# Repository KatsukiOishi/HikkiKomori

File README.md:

# 2022-KawasakiRobot
2022年かわさきロボット

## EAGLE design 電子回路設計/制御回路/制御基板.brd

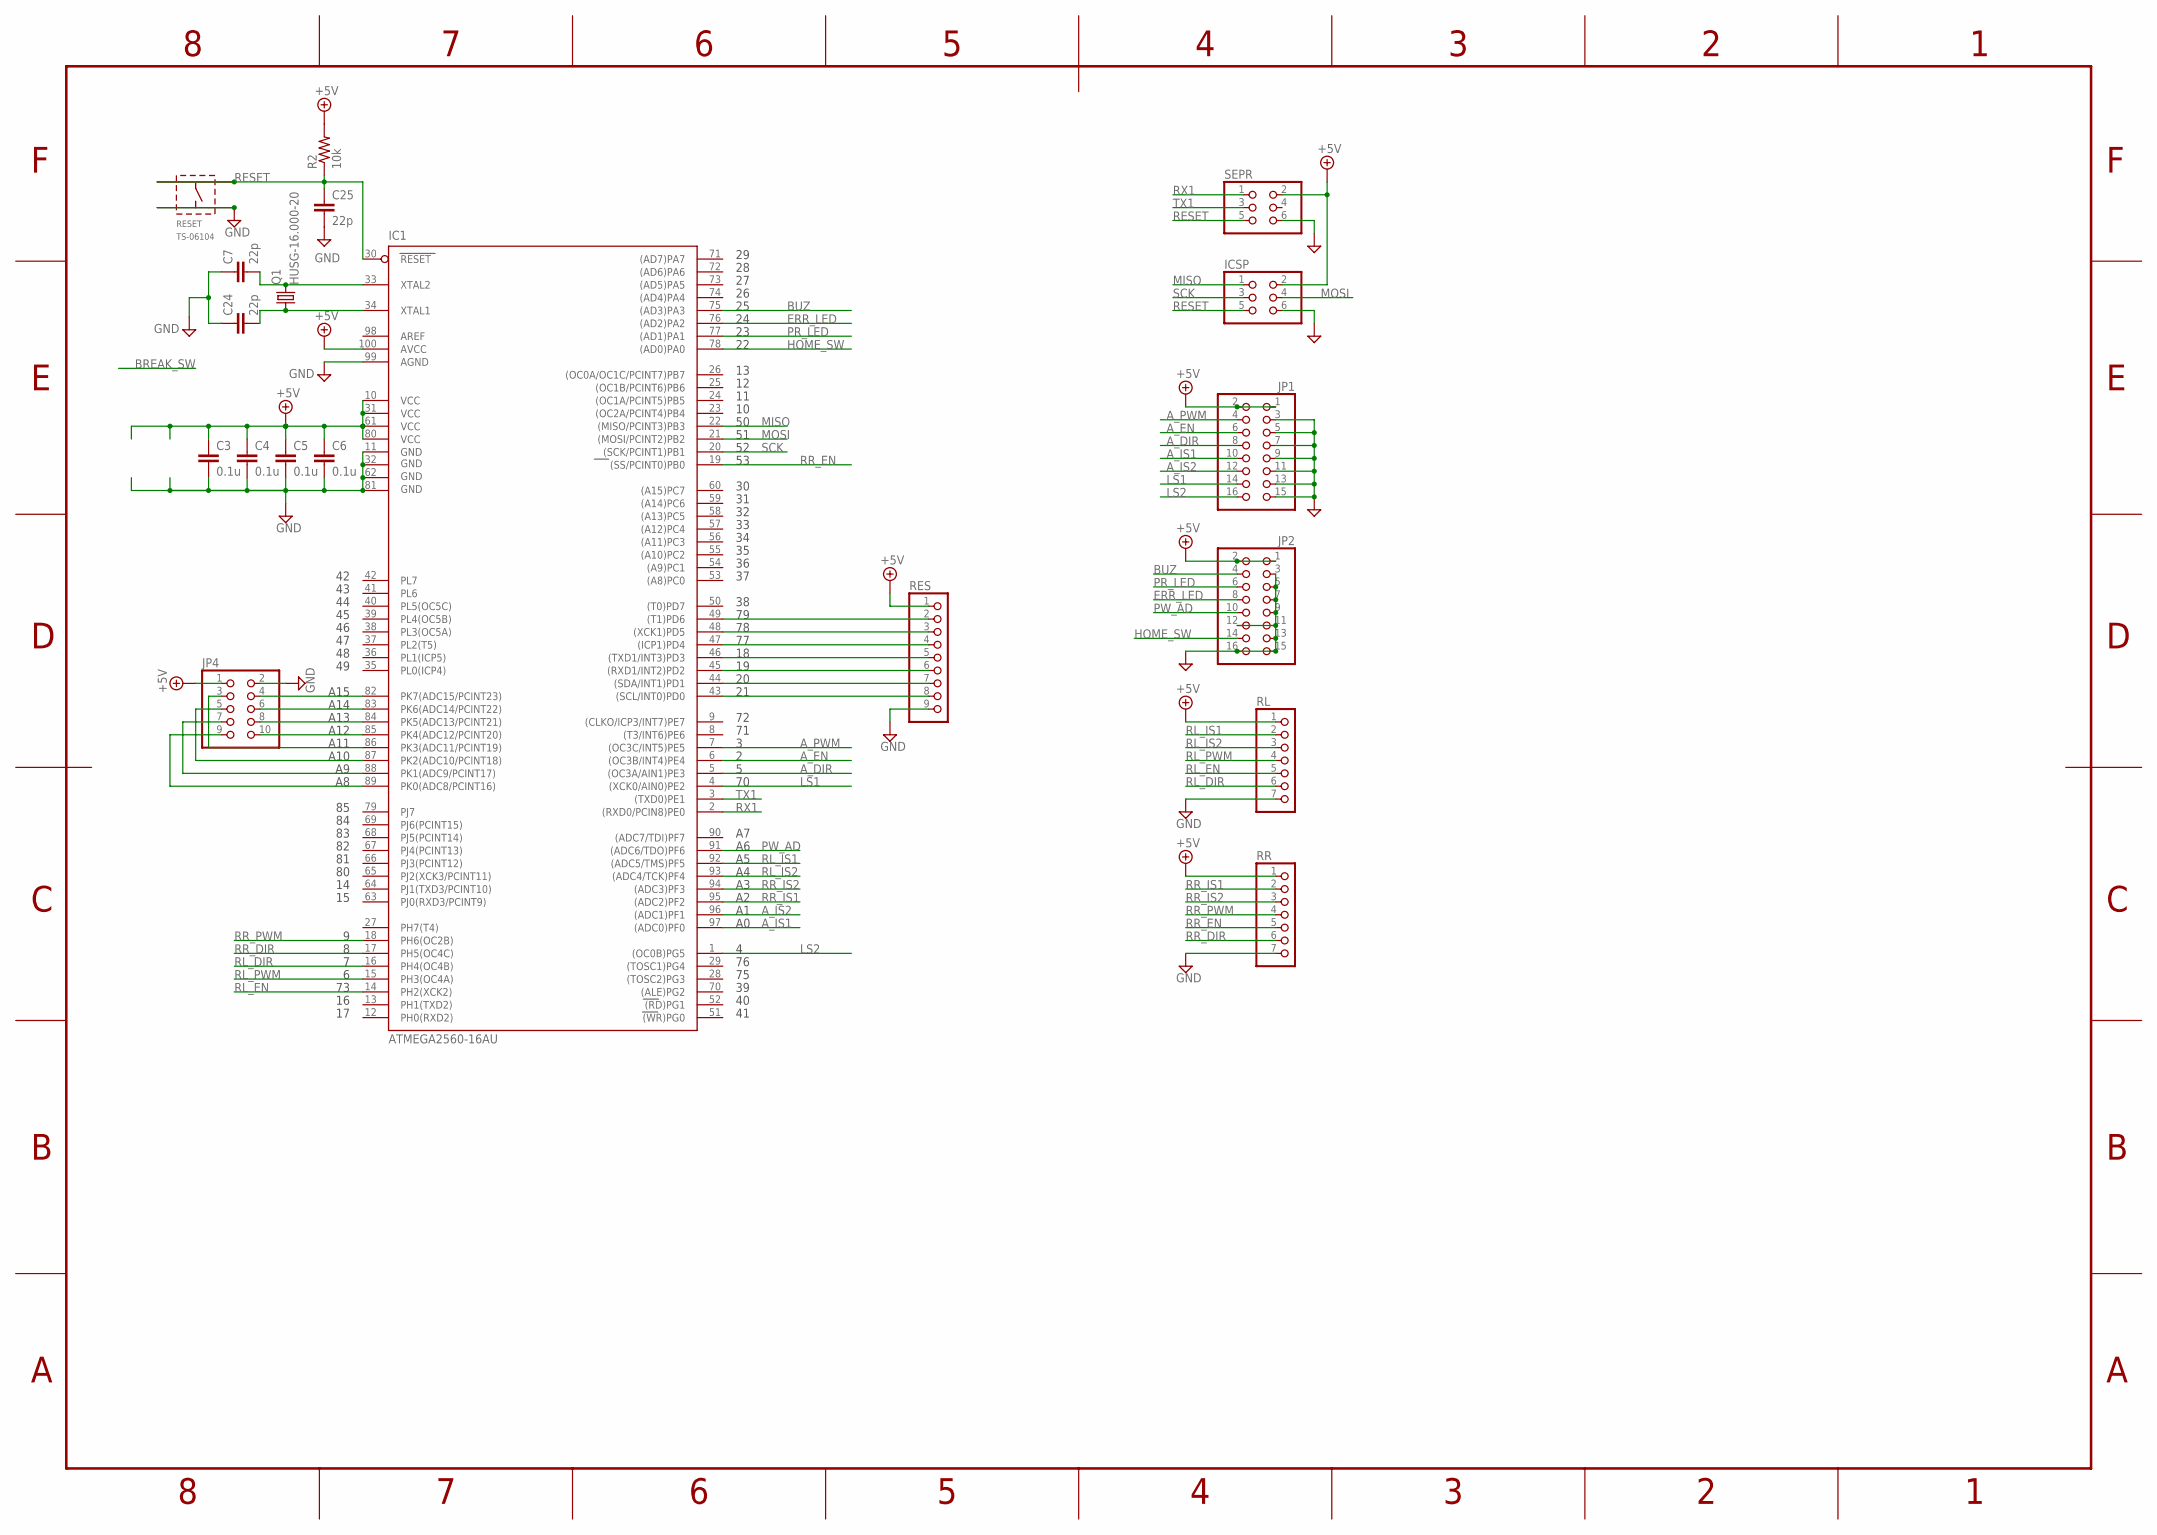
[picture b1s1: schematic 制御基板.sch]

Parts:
C3, C4, C5, C6: 0.1u; C0603
C7, C24, C25: 22p; C0603
IC1: ATMEGA2560-16AU; QFP100
ICSP: PINHD-2X3; 2X03
JP1, JP2: PINHD-2X8; 2X08
JP4: PINHD-2X5; 2X05
Q1: HUSG-16.000-20; XTALRR480W50L990T368H350B
R2: 10k; R0603
RES: PINHD-1X9; 1X09
RESET: TS-06104
RL: PINHD-1X7; 1X07
RR: PINHD-1X7; 1X07
SEPR: PINHD-2X3; 2X03

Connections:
+5V: C3.1, C4.1, C5.1, C6.1, IC1.10 (VCC), IC1.31 (VCC1), IC1.61 (VCC2), IC1.80 (VCC3), IC1.100 (AVCC), ICSP.2, JP1.1, JP1.2, JP2.1, JP2.2, JP4.1, R2.2, RES.1, RL.1, RR.1, SEPR.2
A_DIR: IC1.5 ((OC3A/AIN1)PE3), JP1.8
A_EN: IC1.6 ((OC3B/INT4)PE4), JP1.6
A_IS1: IC1.97 ((ADC0)PF0), JP1.10
A_IS2: IC1.96 ((ADC1)PF1), JP1.12
A_PWM: IC1.7 ((OC3C/INT5)PE5), JP1.4
BUZ: IC1.75 ((AD3)PA3), JP2.4
ERR_LED: IC1.76 ((AD2)PA2), JP2.6
GND: C3.2, C4.2, C5.2, C6.2, C7.1, C24.1, C25.2, IC1.11 (GND), IC1.32 (GND1), IC1.62 (GND2), IC1.81 (GND3), IC1.99 (AGND), ICSP.6, JP1.3, JP1.5, JP1.7, JP1.9, JP1.11, JP1.13, JP1.15, JP2.3, JP2.5, JP2.7, JP2.9, JP2.11, JP2.12, JP2.13, JP2.15, JP2.16, JP4.2, RES.9, RESET.B1 (T3), RESET.B2 (T4), RL.7, RR.7, SEPR.6
HOME_SW: IC1.78 ((AD0)PA0), JP2.14
LS1: IC1.4 ((XCK0/AIN0)PE2), JP1.14
LS2: IC1.1 ((OC0B)PG5), JP1.16
MISO: IC1.22 ((MISO/PCINT3)PB3), ICSP.1
MOSI: IC1.21 ((MOSI/PCINT2)PB2), ICSP.4
unnamed: IC1.43 ((SCL/INT0)PD0), RES.8
unnamed: C24.2, IC1.34 (XTAL1), Q1.1
unnamed: C7.2, IC1.33 (XTAL2), Q1.2
unnamed: IC1.44 ((SDA/INT1)PD1), RES.7
unnamed: IC1.45 ((RXD1/INT2)PD2), RES.6
unnamed: IC1.46 ((TXD1/INT3)PD3), RES.5
unnamed: IC1.47 ((ICP1)PD4), RES.4
unnamed: IC1.48 ((XCK1)PD5), RES.3
unnamed: IC1.49 ((T1)PD6), RES.2
unnamed: IC1.89 (PK0(ADC8/PCINT16)), JP4.9
unnamed: IC1.88 (PK1(ADC9/PCINT17)), JP4.7
unnamed: IC1.87 (PK2(ADC10/PCINT18)), JP4.5
unnamed: IC1.86 (PK3(ADC11/PCINT19)), JP4.3
unnamed: IC1.85 (PK4(ADC12/PCINT20)), JP4.10
unnamed: IC1.84 (PK5(ADC13/PCINT21)), JP4.8
unnamed: IC1.83 (PK6(ADC14/PCINT22)), JP4.6
unnamed: IC1.82 (PK7(ADC15/PCINT23)), JP4.4
PR_LED: IC1.77 ((AD1)PA1), JP2.8
PW_AD: IC1.91 ((ADC6/TDO)PF6), JP2.10
RESET: C25.1, IC1.30 (RESET), ICSP.5, R2.1, RESET.A1 (T1), RESET.A2 (T2), SEPR.5
RL_DIR: IC1.16 (PH4(OC4B)), RL.6
RL_EN: IC1.14 (PH2(XCK2)), RL.5
RL_IS1: IC1.92 ((ADC5/TMS)PF5), RL.2
RL_IS2: IC1.93 ((ADC4/TCK)PF4), RL.3
RL_PWM: IC1.15 (PH3(OC4A)), RL.4
RR_DIR: IC1.17 (PH5(OC4C)), RR.6
RR_EN: IC1.19 ((SS/PCINT0)PB0), RR.5
RR_IS1: IC1.95 ((ADC2)PF2), RR.2
RR_IS2: IC1.94 ((ADC3)PF3), RR.3
RR_PWM: IC1.18 (PH6(OC2B)), RR.4
RX1: IC1.2 ((RXD0/PCIN8)PE0), SEPR.1
SCK: IC1.20 ((SCK/PCINT1)PB1), ICSP.3
TX1: IC1.3 ((TXD0)PE1), SEPR.3

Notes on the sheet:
A10
A11
A12
A15
A14
A13

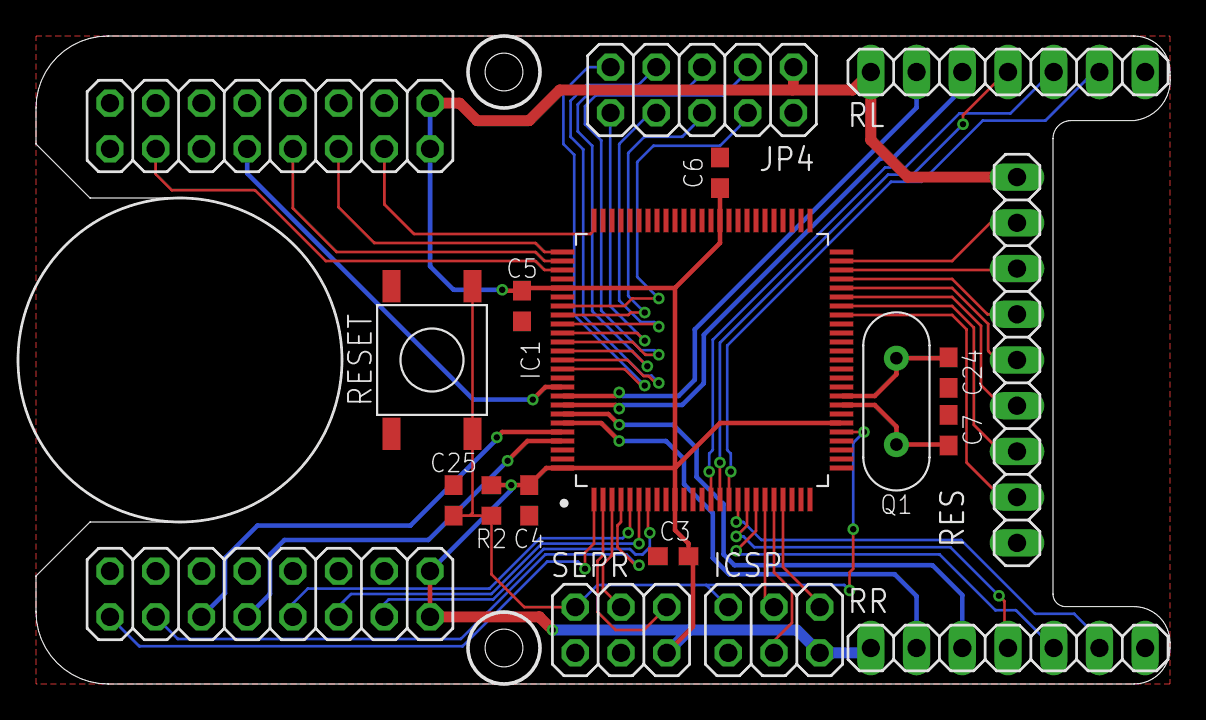
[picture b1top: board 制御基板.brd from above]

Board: 2 copper layers, 63.0 x 36.0 mm, 19 parts (0 on the bottom side), 47 nets.

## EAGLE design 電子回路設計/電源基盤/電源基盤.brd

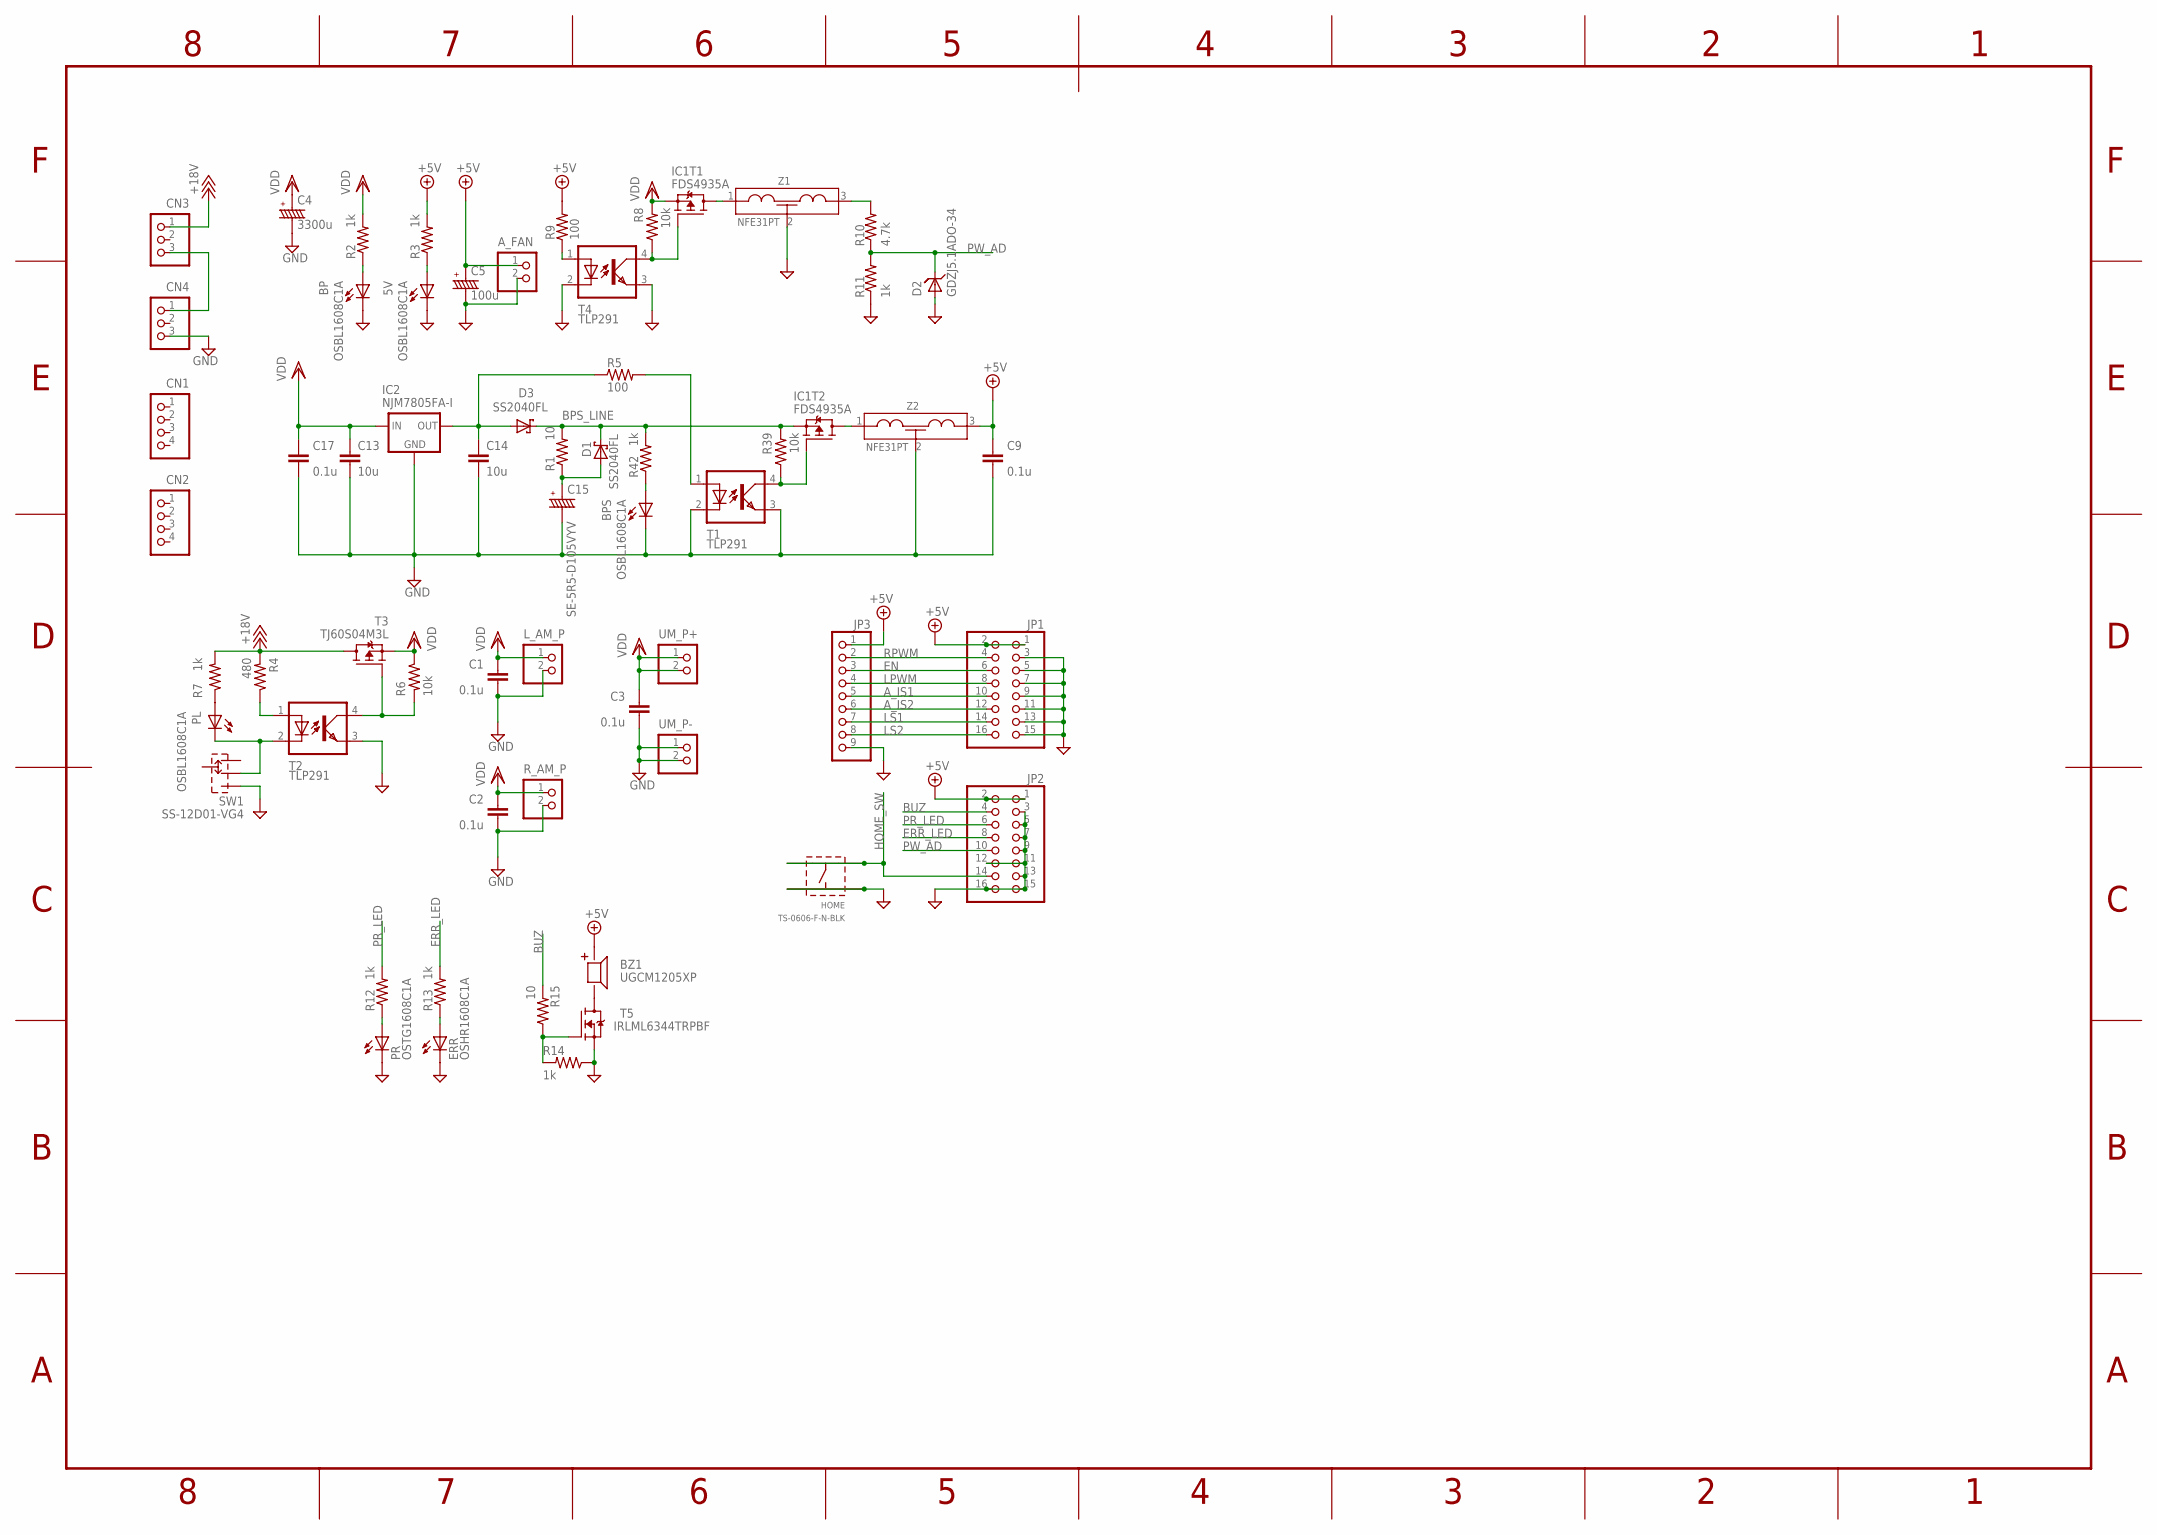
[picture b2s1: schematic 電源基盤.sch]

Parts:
5V: OSBL1608C1A; LEDC1608X39N_B
A_FAN: B2B-XH-A
BP: OSBL1608C1A; LEDC1608X39N_B
BPS: OSBL1608C1A; LEDC1608X39N_B
BZ1: UGCM1205XP
C1, C2, C3, C9, C17: 0.1u; C0603
C4: 3300u; D18_L25_P7.5_D1
C5: 100u; CPOL6.3-7_2.5
C13, C14: 10u; C0805
C15: SE-5R5-D105VYV
CN1, CN2: B4B-XH-A
CN3, CN4: B3P-VH
D1, D3: SS2040FL; SOD-123
D2: GDZJ5.1ADO-34; DIOAD590W50L290D210B
ERR: OSHR1608C1A; LEDC1608X39N_R
HOME: TS-0606-F-N-BLK; TS-0606-F-N
IC1: FDS4935A; SOIC127P600X250-8N
IC2: NJM7805FA-I; TO220
JP1, JP2: PINHD-2X8; 2X08
JP3: PINHD-1X9; 1X09
L_AM_P: B2P-VH
PL: OSBL1608C1A; LEDC1608X39N_B
PR: OSTG1608C1A; LEDC1608X39N_G
R1, R15: 10; R0603
R2, R3, R7, R11, R12, R13, R14, R42: 1k; R0603
R4: 480; R0603
R5, R9: 100; R0603
R6, R8, R39: 10k; R0603
R10: 4.7k; R0603
R_AM_P: B2P-VH
SW1: SS-12D01-VG4
T1, T2, T4: TLP291; SOIC127P700X210-4N
T3: TJ60S04M3L; DPACK
T5: IRLML6344TRPBF; SOT95P240X110-3N
UM_P+: B2P-VH
UM_P-: B2P-VH
Z1, Z2: NFE31PT; NFE31

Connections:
5V1: IC1.7 (D), IC1.8 (D), Z2.1
+5V: A_FAN.1, BZ1.+, C5.+, C9.1, JP1.1, JP1.2, JP2.1, JP2.2, JP3.1, R3.2, R9.2, Z2.3
+18V: CN3.1, R4.2, R7.2, T3.2 (D)
A_IS1: JP1.10, JP3.5
A_IS2: JP1.12, JP3.6
BLINE2: CN3.3, CN4.1
BPS_LINE: D1.1 (C), D3.1 (C), IC1.1 (S), R1.2, R39.2, R42.2
BPS_OR: C15.+, D1.2 (A), R1.1
BUZ: JP2.4, R15.2
EN: JP1.6, JP3.3
ERR_LED: JP2.6, R13.2
GND: 5V.2 (C), A_FAN.2, BP.2 (C), BPS.2 (C), C1.2, C2.2, C3.2, C4.-, C5.-, C9.2, C13.2, C14.2, C15.-, C17.2, CN4.3, D2.2 (A), ERR.2 (C), HOME.T3, HOME.T4, IC2.2 (GND), JP1.3, JP1.5, JP1.7, JP1.9, JP1.11, JP1.13, JP1.15, JP2.3, JP2.5, JP2.7, JP2.9, JP2.11, JP2.12, JP2.13, JP2.15, JP2.16, JP3.9, L_AM_P.2, PR.K (C), R11.1, R14.1, R_AM_P.2, SW1.NO, T1.2 (C), T1.3 (EMIT), T2.3 (EMIT), T4.2 (C), T4.3 (EMIT), T5.2 (S), UM_P-.1, UM_P-.2, Z1.2, Z2.2
HOME_SW: HOME.T1, HOME.T2, JP2.14
LPWM: JP1.8, JP3.4
LS1: JP1.14, JP3.7
LS2: JP1.16, JP3.8
unnamed: PL.1 (A), R7.1
unnamed: BP.1 (A), R2.1
unnamed: 5V.1 (A), R3.1
unnamed: IC1.5 (D), IC1.6 (D), Z1.1
unnamed: C14.1, D3.2 (A), IC2.3 (OUT), R5.1
unnamed: R4.1, T2.1 (A)
unnamed: PL.2 (C), SW1.COM, T2.2 (C)
unnamed: R6.2, T2.4 (COL), T3.1 (G)
unnamed: IC1.4 (G), R8.1, T4.4 (COL)
unnamed: PR.A, R12.1
unnamed: R9.1, T4.1 (A)
unnamed: R10.2, Z1.3
unnamed: IC1.2 (G), R39.1, T1.4 (COL)
unnamed: ERR.1 (A), R13.1
unnamed: BZ1.-, T5.3 (D)
unnamed: R14.2, R15.1, T5.1 (G)
unnamed: R5.2, T1.1 (A)
unnamed: BPS.1 (A), R42.1
PR_LED: JP2.8, R12.2
PW_AD: D2.1 (C), JP2.10, R10.1, R11.2
RPWM: JP1.4, JP3.2
VDD: C1.1, C2.1, C3.1, C4.+, C13.1, C17.1, IC1.3 (S), IC2.1 (IN), L_AM_P.1, R2.2, R6.1, R8.2, R_AM_P.1, T3.3 (S), UM_P+.1, UM_P+.2

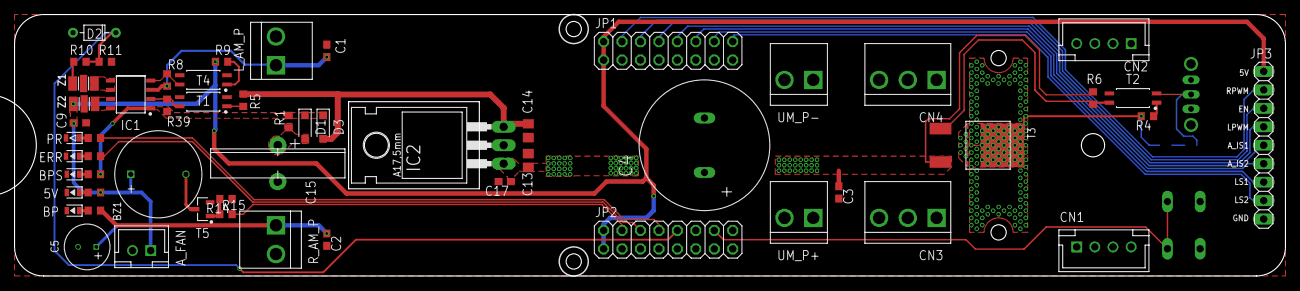
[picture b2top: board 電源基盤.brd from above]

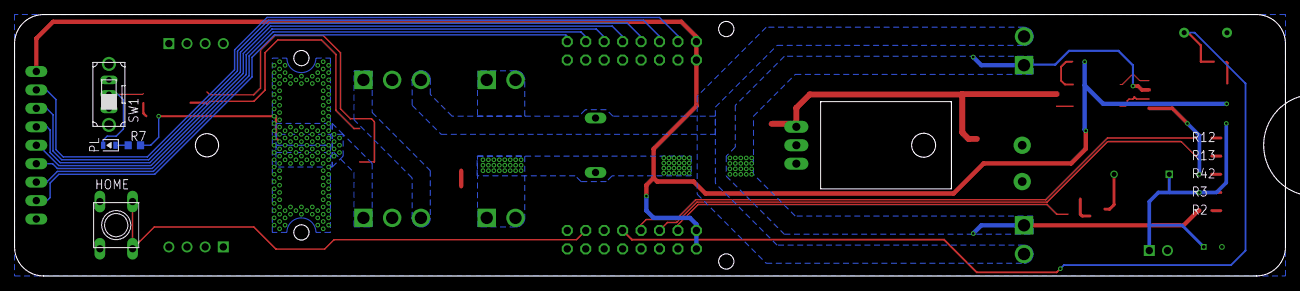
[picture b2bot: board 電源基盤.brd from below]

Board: 2 copper layers, 175.0 x 36.0 mm, 60 parts (4 on the bottom side), 38 nets.

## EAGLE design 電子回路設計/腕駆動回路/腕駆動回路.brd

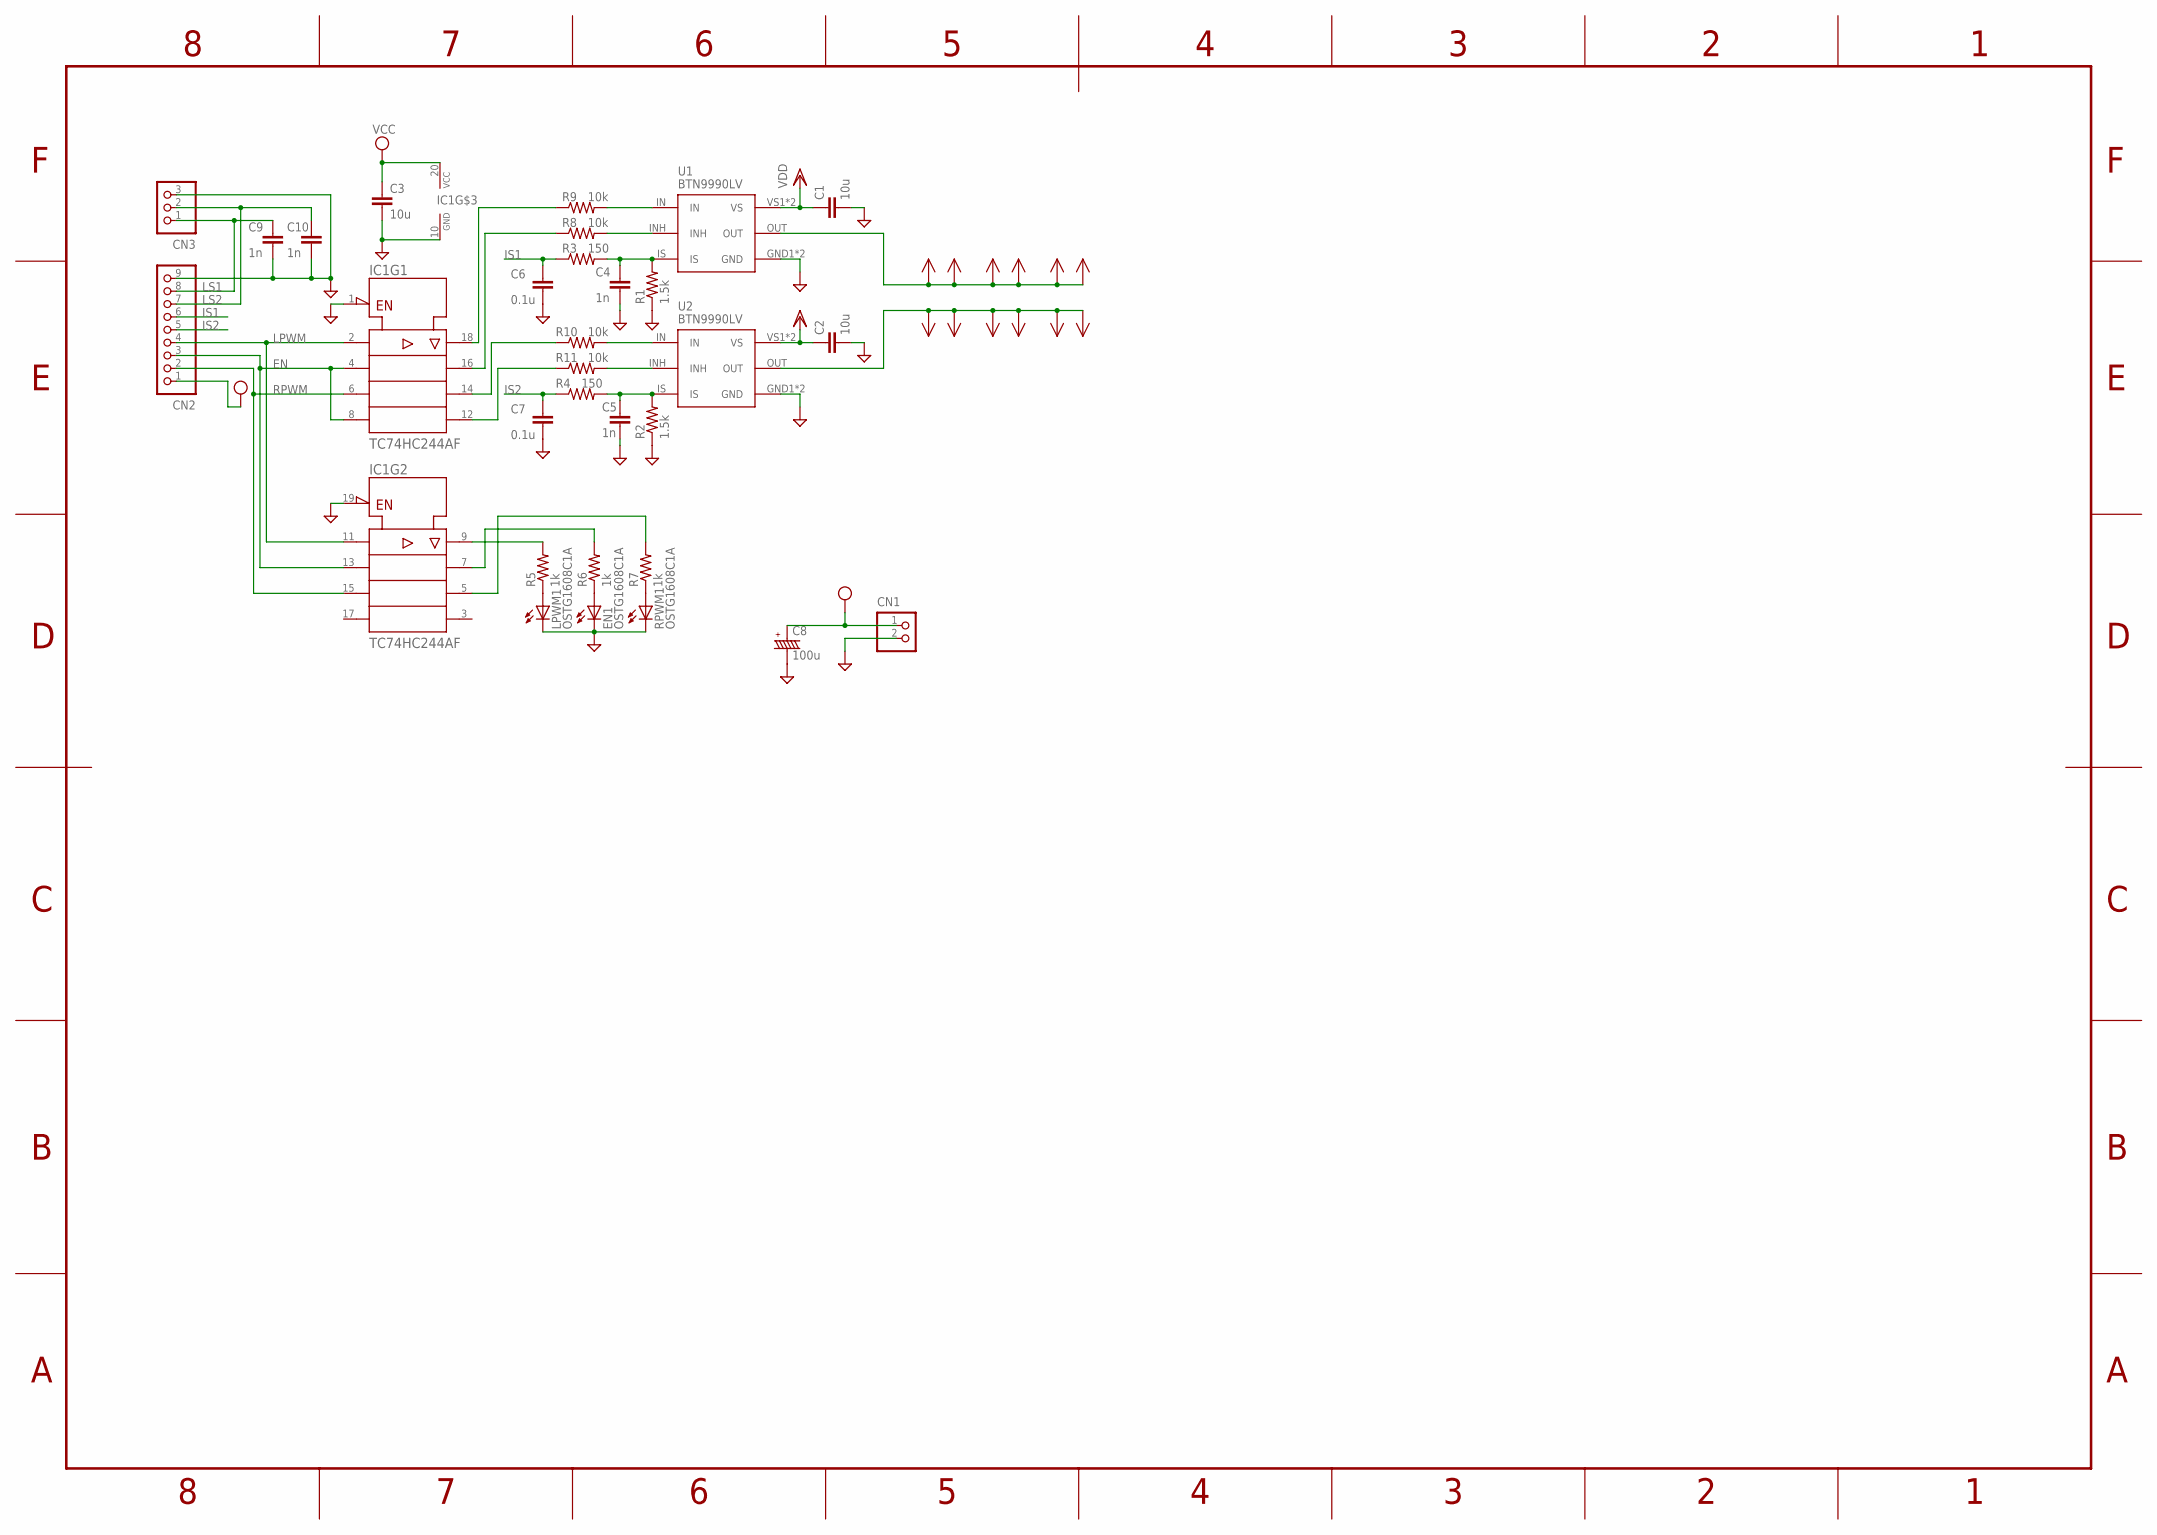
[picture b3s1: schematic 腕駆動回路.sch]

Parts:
C1, C2, C3: 10u; C3216
C4, C5, C9, C10: 1n; C1608
C6, C7: 0.1u; C1608
C8: 100u; CPOL6.3-7_2.5
CN1: B2B-XH-A
CN2: B9B-XH-A
CN3: B3B-XH-A
EN1: OSTG1608C1A; LEDC1608X39N_G
IC1: TC74HC244AF; SOP20
LPWM1: OSTG1608C1A; LEDC1608X39N_G
OUT1: VIA_2.5X5.25_D0.75; VIA_2X5.25_D0.75
R1, R2: 1.5k; R0603
R3, R4: 150; R0603
R5, R6, R7: 1k; R0603
R8, R9, R10, R11: 10k; R1608
RPWM1: OSTG1608C1A; LEDC1608X39N_G
U1, U2: BTN9990LV
U$2, U$4, U$5, U$6, U$7, U$8, U$9, U$10, U$11, U$12, U$13: VIA_2.5X5.25_D0.75; VIA_2X5.25_D0.75

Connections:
EN: CN2.3, IC1.4 (A2), IC1.8 (A4), IC1.13 (A2)
GND: C1.2, C2.2, C3.2, C4.2, C5.2, C6.2, C7.2, C8.-, C9.2, C10.2, CN1.2, CN2.9, CN3.3, EN1.K (C), IC1.1 (!G), IC1.10 (GND), IC1.19 (!G), LPWM1.K (C), R1.1, R2.1, RPWM1.K (C), U1.GND1 (GND), U1.GND2 (GND), U2.GND1 (GND), U2.GND2 (GND)
IS1: C6.1, CN2.6, R3.1
IS1_A: C4.1, R1.2, R3.2, U1.IS
IS2: C7.1, CN2.5, R4.1
IS2_1: C5.1, R2.2, R4.2, U2.IS
LPWM: CN2.4, IC1.2 (A1), IC1.11 (A1)
LS1: C9.1, CN2.8, CN3.1
LS2: C10.1, CN2.7, CN3.2
unnamed: IC1.18 (Y1), R9.1
unnamed: IC1.16 (Y2), R8.1
unnamed: IC1.14 (Y3), R10.1
unnamed: IC1.12 (Y4), R11.1
unnamed: LPWM1.A, R5.1
unnamed: EN1.A, R6.1
unnamed: R7.1, RPWM1.A
unnamed: IC1.9 (Y1), R5.2
unnamed: IC1.7 (Y2), R6.2
unnamed: IC1.5 (Y3), R7.2
unnamed: R8.2, U1.INH
unnamed: R9.2, U1.IN
unnamed: R10.2, U2.IN
unnamed: R11.2, U2.INH
OUT1: OUT1.P$1, U1.OUT, U$2.P$1, U$4.P$1, U$5.P$1, U$6.P$1, U$7.P$1
OUT2: U2.OUT, U$8.P$1, U$9.P$1, U$10.P$1, U$11.P$1, U$12.P$1, U$13.P$1
RPWM: CN2.2, IC1.6 (A3), IC1.15 (A3)
VCC: C3.1, C8.+, CN1.1, CN2.1, IC1.20 (VCC)
VDD: C1.1, C2.1, U1.VS1 (VS), U1.VS2 (VS), U2.VS1 (VS), U2.VS2 (VS)

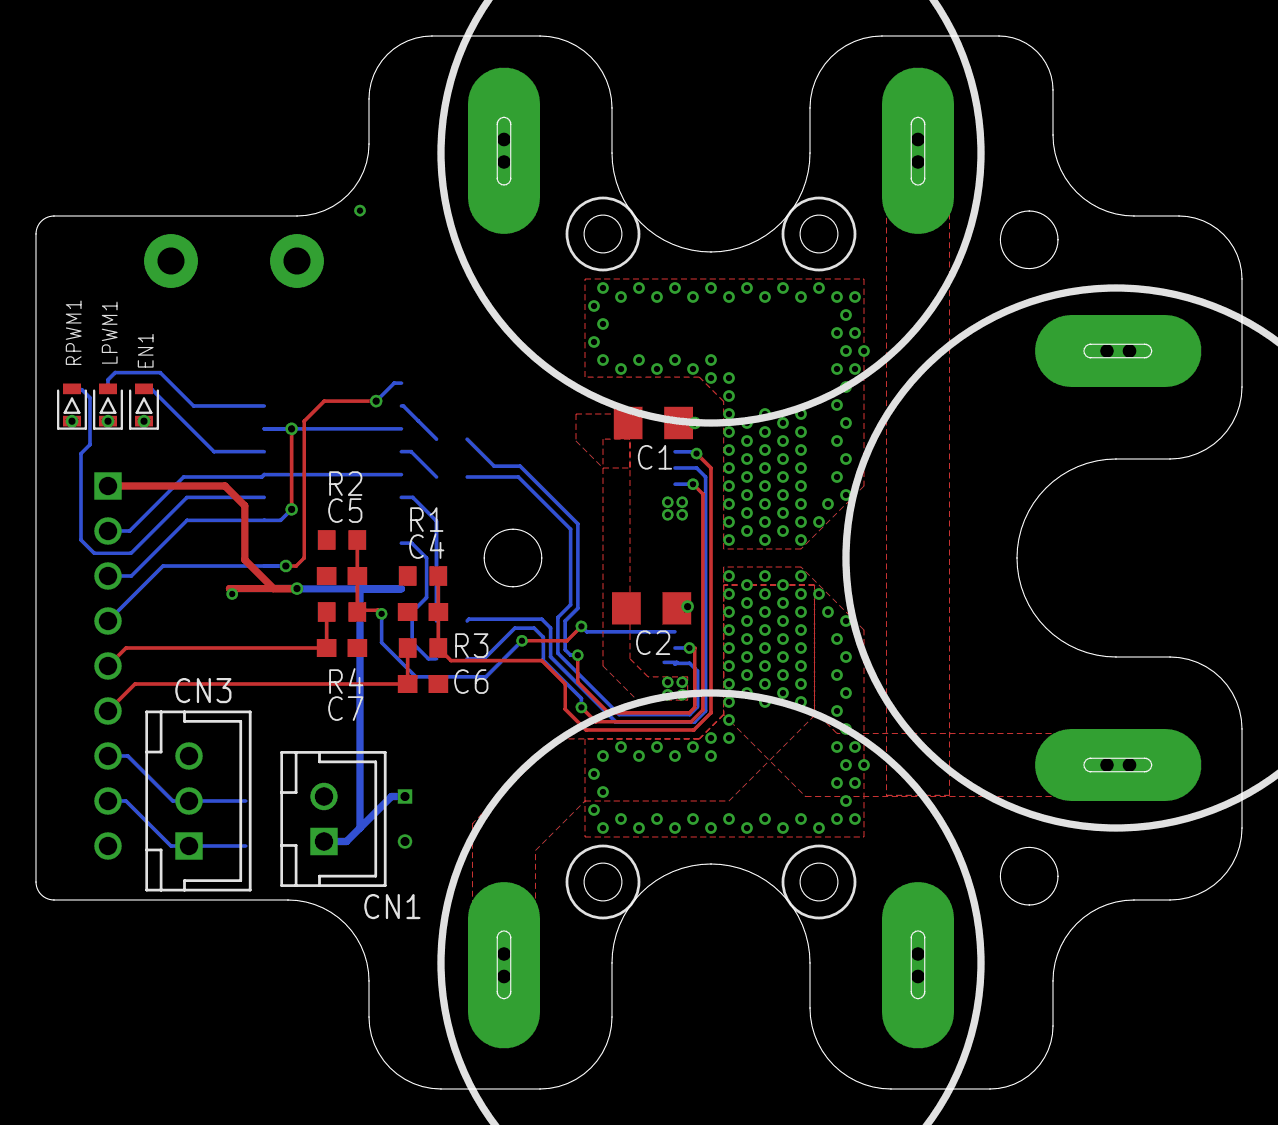
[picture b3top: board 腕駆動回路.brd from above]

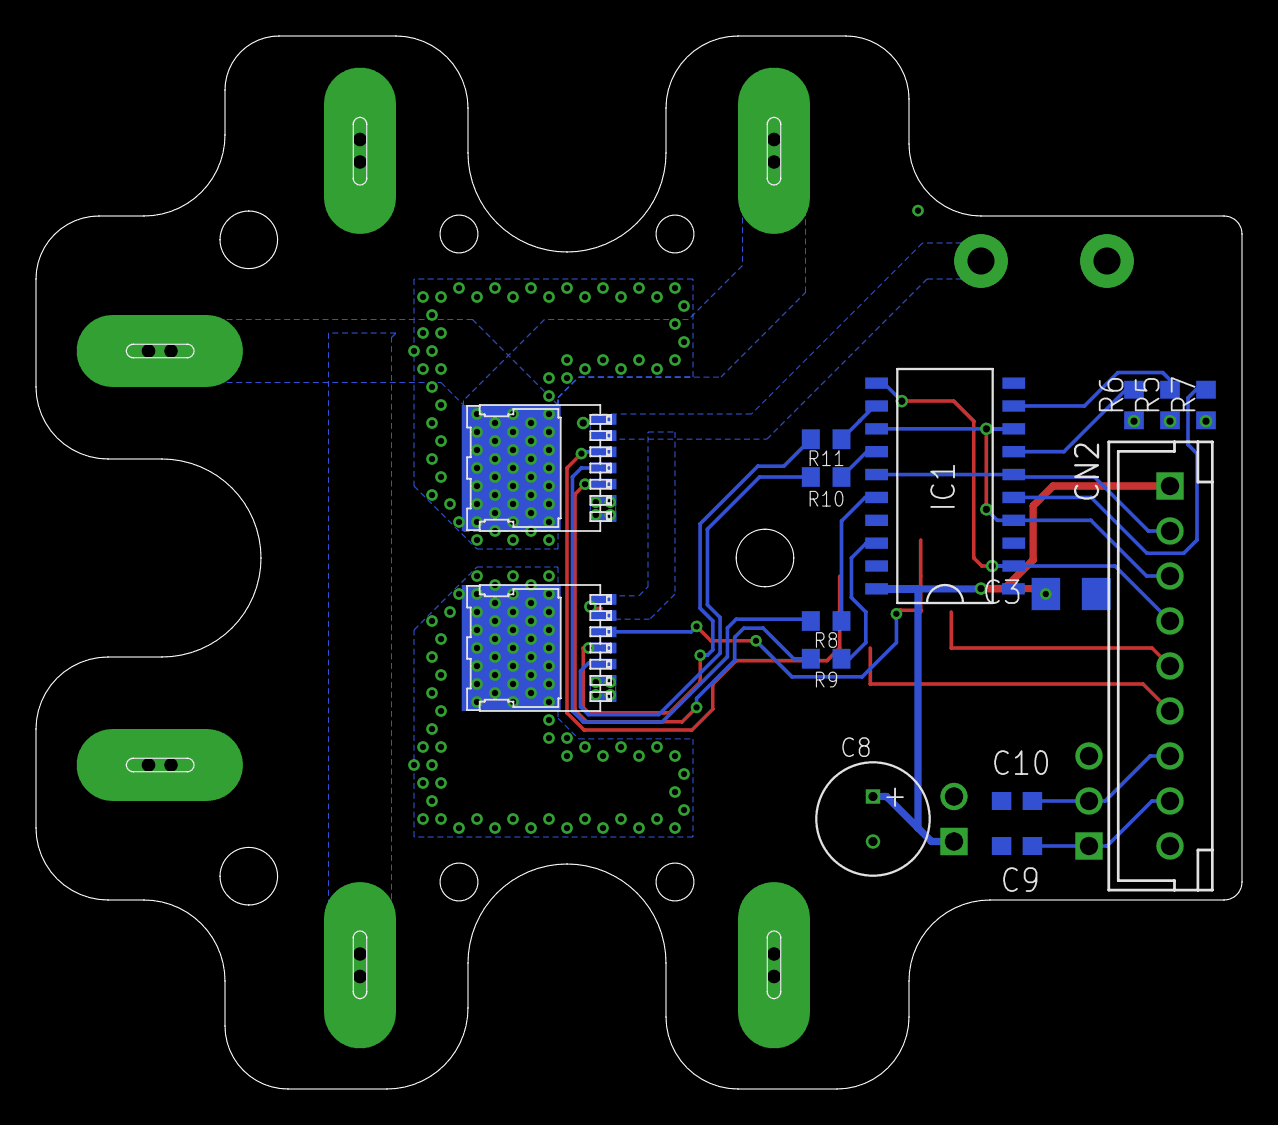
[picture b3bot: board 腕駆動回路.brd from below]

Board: 2 copper layers, 67.0 x 58.5 mm, 42 parts (15 on the bottom side), 28 nets.
